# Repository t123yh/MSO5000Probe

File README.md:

# Pod for Rigol MSO5000 Logic Analyzer

This is a pod for MSO5000. All components are in JLC SMT basic library.

See also [Original Project](https://gitlab.com/thmjpr/stm32f03_la_monitor/tree/master/PCB_Rev2).

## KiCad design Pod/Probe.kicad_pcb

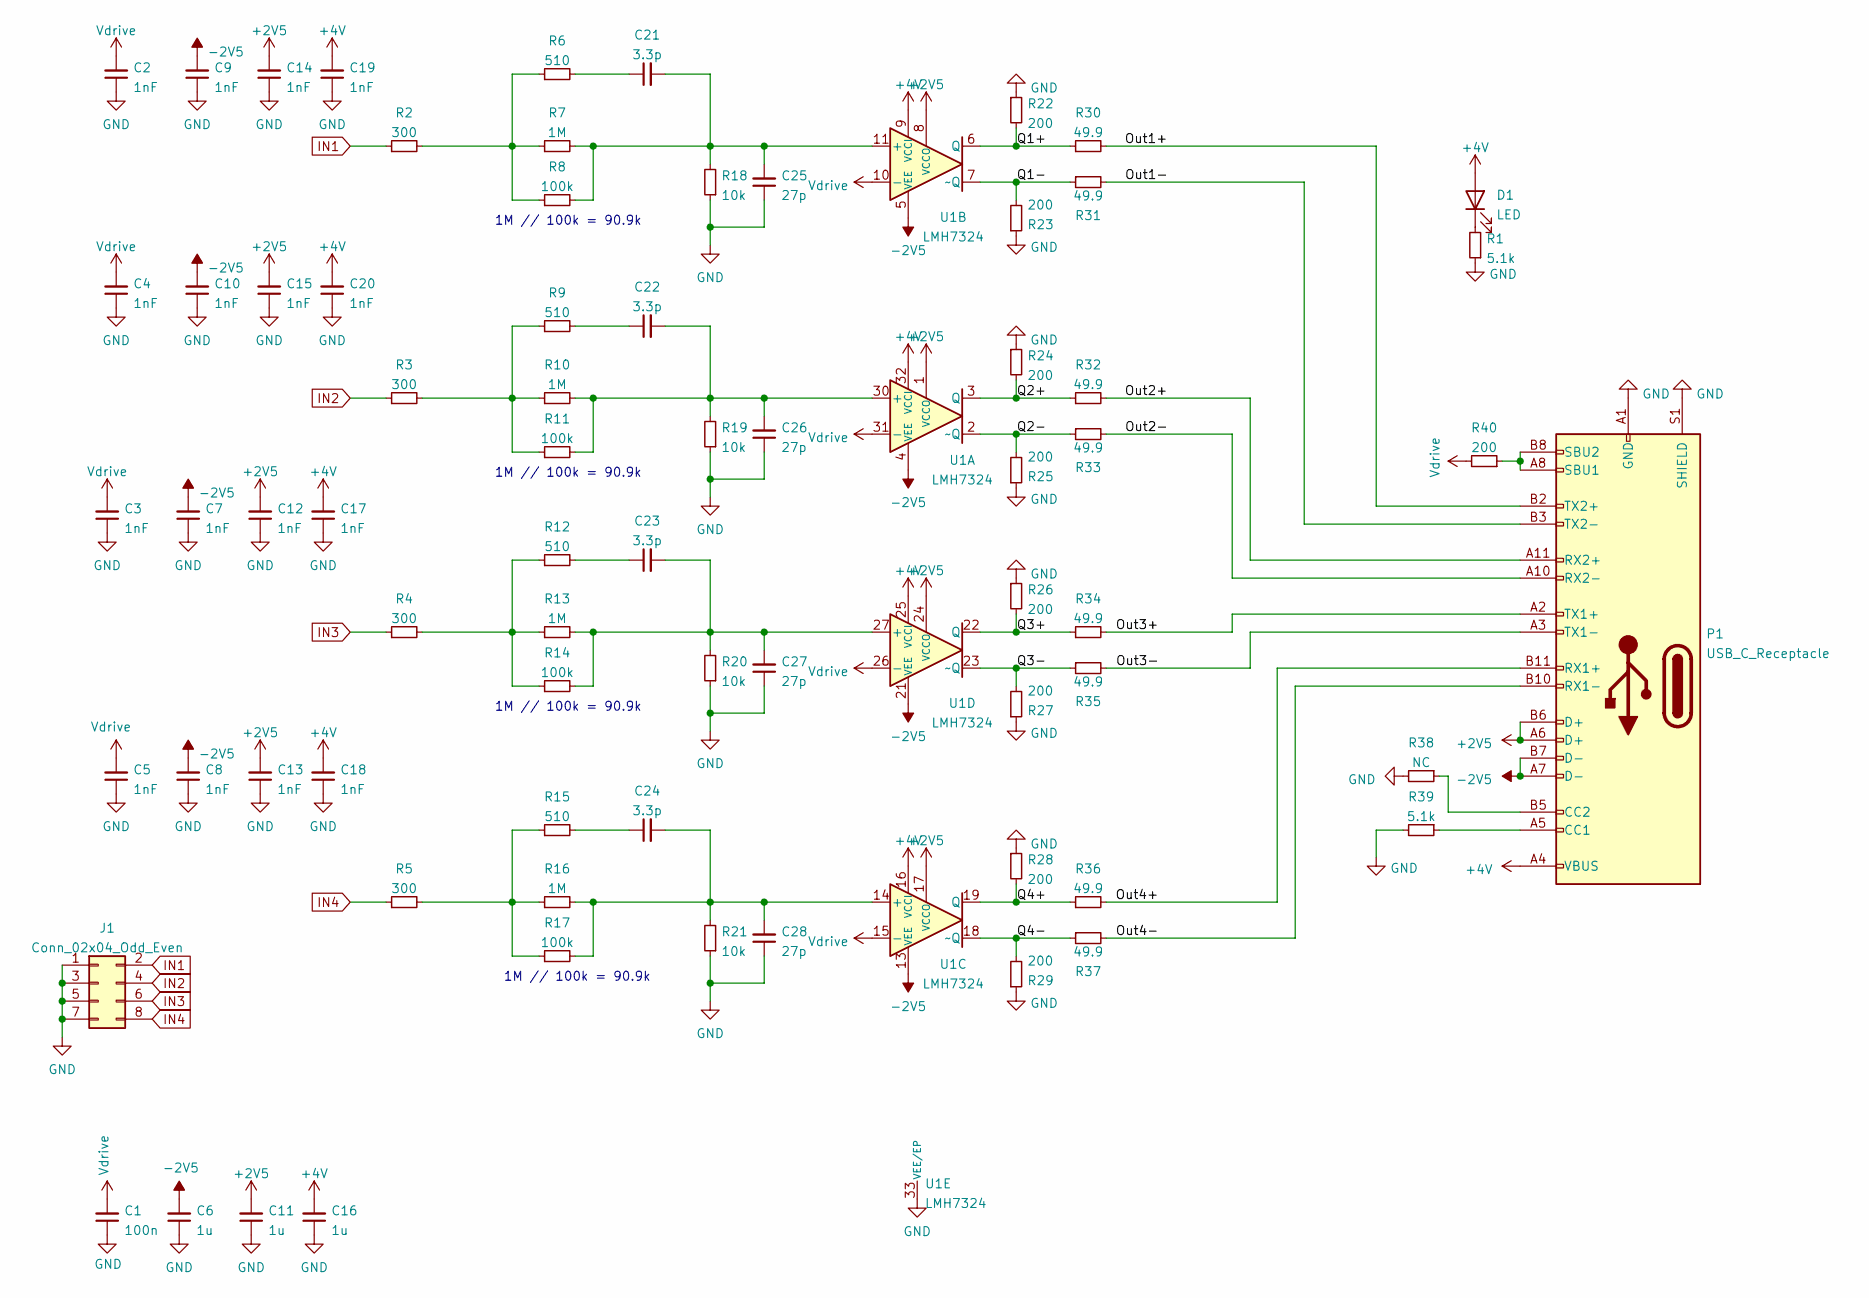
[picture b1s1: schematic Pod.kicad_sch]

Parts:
C1: 100n; 0402_C
C2, C3, C4, C5, C7, C8, C9, C10, C12, C13, C14, C15, C17, C18, C19, C20: 1nF; 0402_C
C6, C11, C16: 1u; 0402_C
C21, C22, C23, C24: 3.3p; 0402_C
C25, C26, C27, C28: 27p; 0402_C
D1: LED; 0805_LED_S1_NUM
J1: Conn_02x04_Odd_Even; PinHeader_2x04_P2.54mm_Vertical
P1: USB_C_Receptacle; USB_C_Receptacle_Amphenol_12401548E4-2A
R1, R39: 5.1k; 0402_R
R2, R3, R4, R5: 300; 0402_R
R6, R9, R12, R15: 510; 0402_R
R7, R10, R13, R16: 1M; 0402_R
R8, R11, R14, R17: 100k; 0402_R
R18, R19, R20, R21: 10k; 0402_R
R22, R23, R24, R25, R26, R27, R28, R29, R40: 200; 0402_R
R30, R31, R32, R33, R34, R35, R36, R37: 49.9; 0402_R
R38: NC; 0402_R
U1: LMH7324; WQFN-32-1EP_5x5mm_P0.5mm_EP3.1x3.1mm

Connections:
+2V5: C11.2, C12.2, C13.2, C14.2, C15.2, P1.A6 (D+), P1.B6 (D+), U1.1 (VCCO), U1.8 (VCCO), U1.17 (VCCO), U1.24 (VCCO)
+4V: C16.2, C17.2, C18.2, C19.2, C20.2, D1.2 (A), P1.A4 (VBUS), P1.A9 (VBUS), P1.B4 (VBUS), P1.B9 (VBUS), U1.9 (VCCI), U1.16 (VCCI), U1.25 (VCCI), U1.32 (VCCI)
-2V5: C6.2, C7.2, C8.2, C9.2, C10.2, P1.A7 (D-), P1.B7 (D-), U1.4 (VEE), U1.5 (VEE), U1.12 (VEE), U1.13 (VEE), U1.20 (VEE), U1.21 (VEE), U1.28 (VEE), U1.29 (VEE)
/Out1+: P1.B2 (TX2+), R30.2
/Out1-: P1.B3 (TX2-), R31.2
/Out2+: P1.A11 (RX2+), R32.2
/Out2-: P1.A10 (RX2-), R33.2
/Out3+: P1.A2 (TX1+), R34.2
/Out3-: P1.A3 (TX1-), R35.2
/Out4+: P1.B11 (RX1+), R36.2
/Out4-: P1.B10 (RX1-), R37.2
/Q1+: R22.2, R30.1, U1.6 (Q)
/Q1-: R23.2, R31.1, U1.7 (~Q)
/Q2+: R24.2, R32.1, U1.3 (Q)
/Q2-: R25.2, R33.1, U1.2 (~Q)
/Q3+: R26.2, R34.1, U1.22 (Q)
/Q3-: R27.2, R35.1, U1.23 (~Q)
/Q4+: R28.2, R36.1, U1.19 (Q)
/Q4-: R29.2, R37.1, U1.18 (~Q)
GND: C1.1, C2.1, C3.1, C4.1, C5.1, C6.1, C7.1, C8.1, C9.1, C10.1, C11.1, C12.1, C13.1, C14.1, C15.1, C16.1, C17.1, C18.1, C19.1, C20.1, C25.1, C26.1, C27.1, C28.1, J1.1, J1.3, J1.5, J1.7, P1.A1 (GND), P1.A12 (GND), P1.B1 (GND), P1.B12 (GND), P1.S1 (SHIELD), R1.1, R18.1, R19.1, R20.1, R21.1, R22.1, R23.1, R24.1, R25.1, R26.1, R27.1, R28.1, R29.1, R38.2, R39.2, U1.33 (VEE/EP)
IN1: J1.2, R2.1
IN2: J1.4, R3.1
IN3: J1.6, R4.1
IN4: J1.8, R5.1
unnamed: C21.1, R6.2
unnamed: C21.2, C25.2, R7.2, R8.2, R18.2, U1.11 (+)
unnamed: C22.1, R9.2
unnamed: C22.2, C26.2, R10.2, R11.2, R19.2, U1.30 (+)
unnamed: C23.1, R12.2
unnamed: C23.2, C27.2, R13.2, R14.2, R20.2, U1.27 (+)
unnamed: C24.1, R15.2
unnamed: C24.2, C28.2, R16.2, R17.2, R21.2, U1.14 (+)
unnamed: D1.1 (K), R1.2
unnamed: R2.2, R6.1, R7.1, R8.1
unnamed: R3.2, R9.1, R10.1, R11.1
unnamed: R4.2, R12.1, R13.1, R14.1
unnamed: R5.2, R15.1, R16.1, R17.1
unnamed: P1.B5 (CC2), R38.1
unnamed: P1.A5 (CC1), R39.1
unnamed: P1.A8 (SBU1), P1.B8 (SBU2), R40.1
Vdrive: C1.2, C2.2, C3.2, C4.2, C5.2, R40.2, U1.10 (-), U1.15 (-), U1.26 (-), U1.31 (-)

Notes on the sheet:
1M // 100k = 90.9k

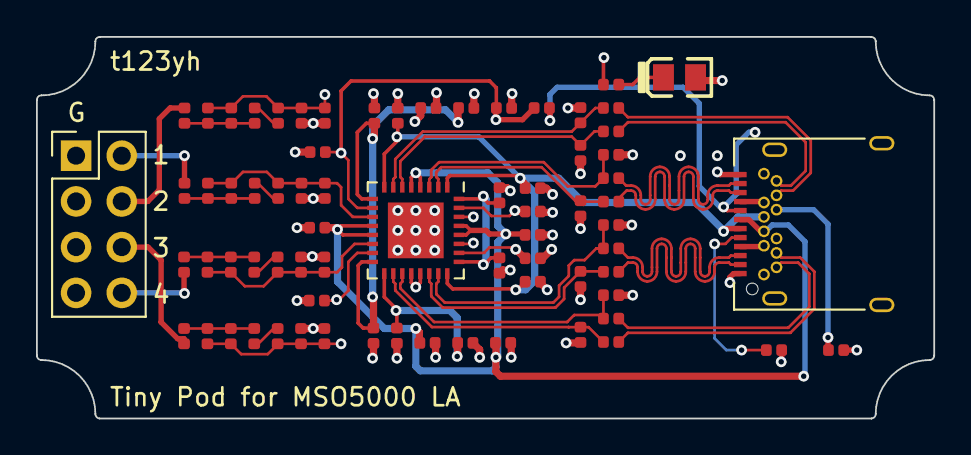
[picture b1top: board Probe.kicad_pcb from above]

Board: 4 copper layers, 49.8 x 21.2 mm, 72 parts (0 on the bottom side), 41 nets.

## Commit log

2021-08-06 Initial
2021-08-06 Add README
2021-08-06 Add images
2021-08-06 Rename project
